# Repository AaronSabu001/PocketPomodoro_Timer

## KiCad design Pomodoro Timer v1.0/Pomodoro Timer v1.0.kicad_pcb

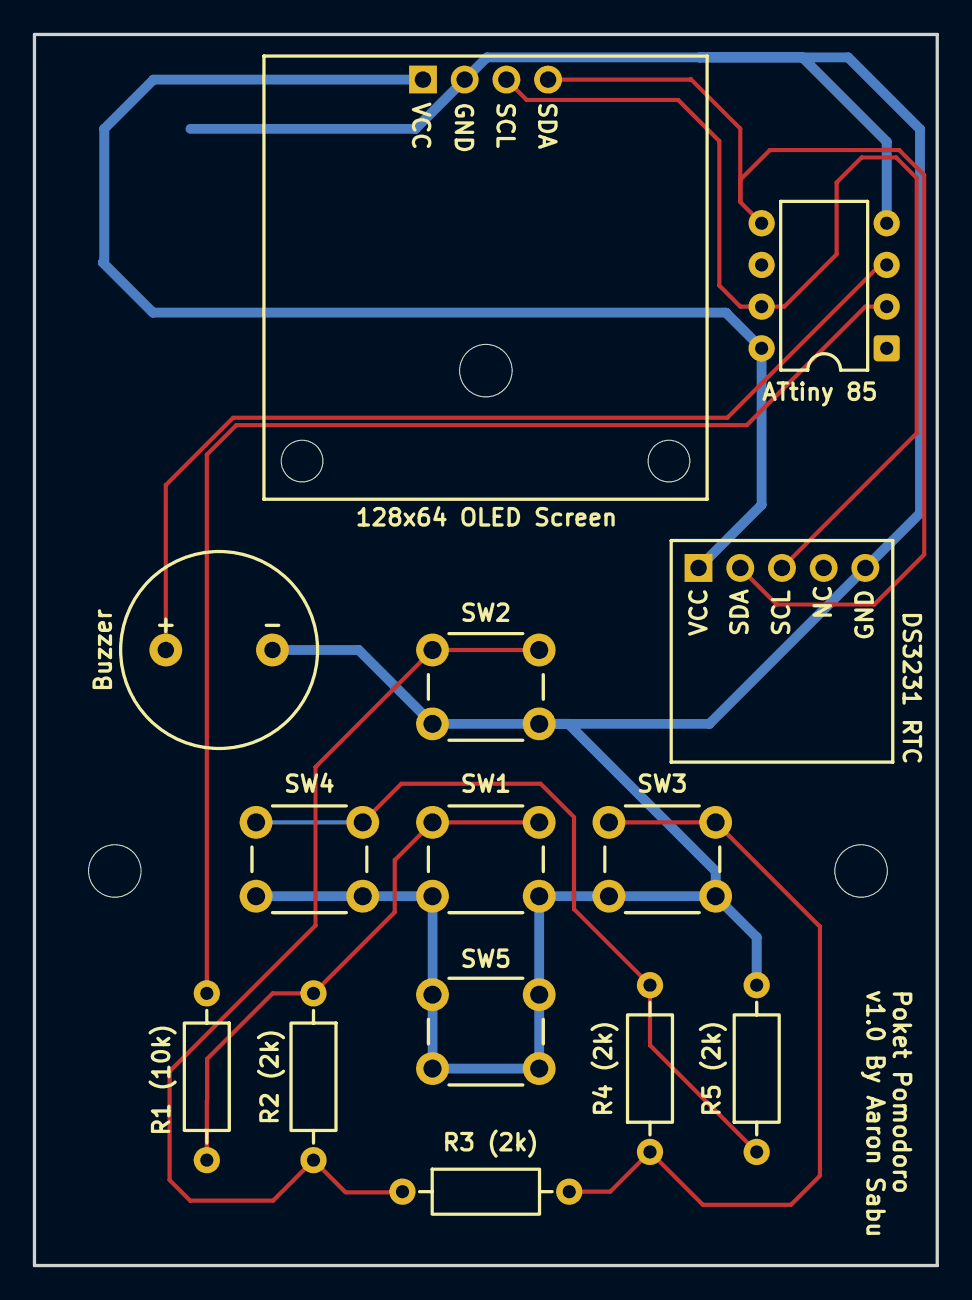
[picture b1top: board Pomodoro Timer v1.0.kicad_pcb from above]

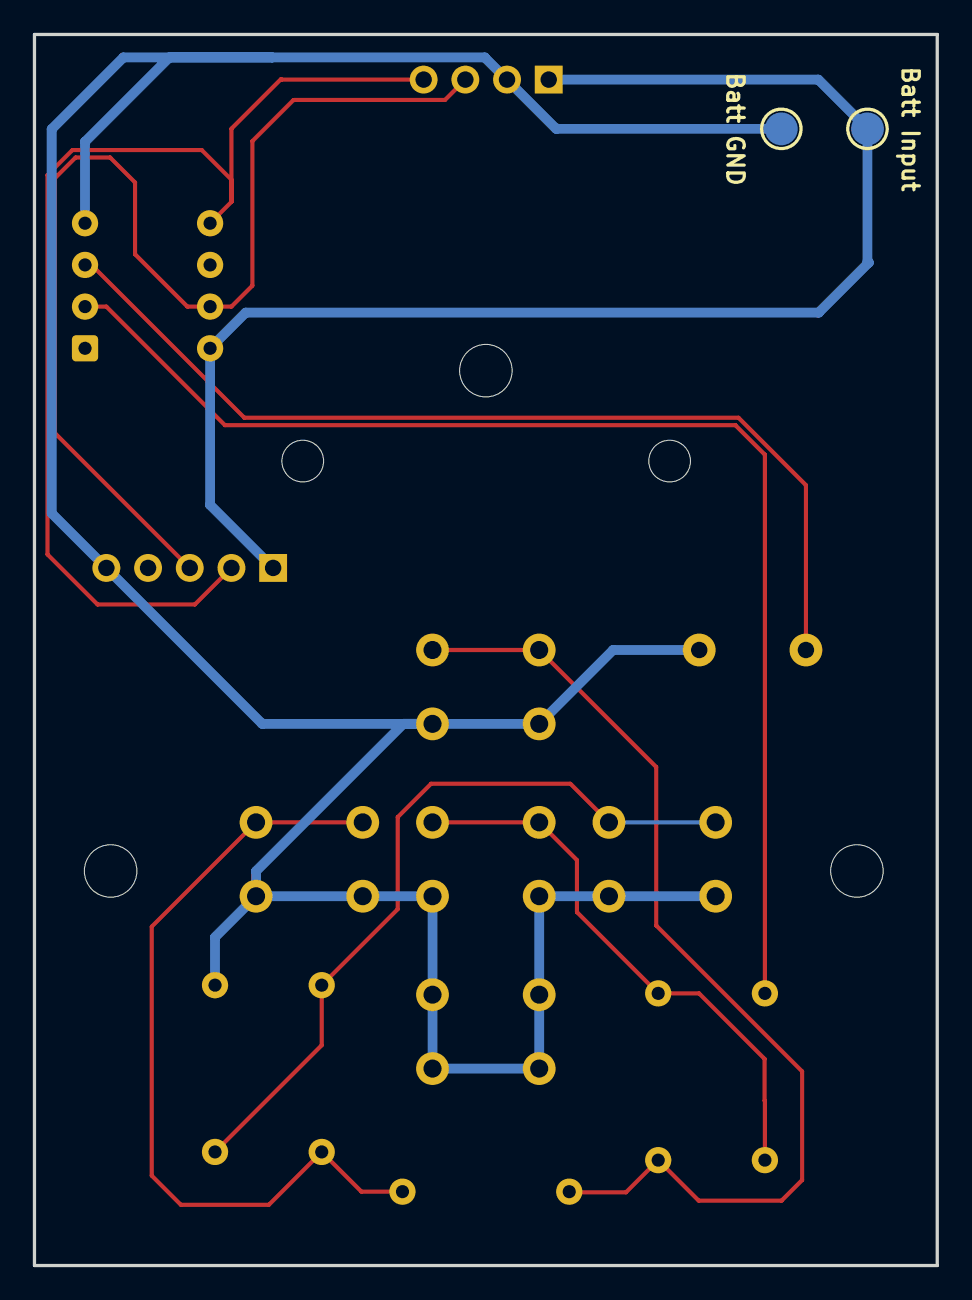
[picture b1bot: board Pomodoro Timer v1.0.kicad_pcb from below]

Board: 4 copper layers, 55.0 x 75.0 mm, 18 parts (2 on the bottom side), 10 nets.

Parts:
128x64 OLED Screen: 128x64 OLED; SSD1306_OLED_Module _I2C
ATtiny 85: ATtiny85-20P; DIP-8_W7.62mm
Batt GND: BT_Pad_Neg; TestPoint_Pad_D2.0mm
Batt Input: BT_Pad_Pos; TestPoint_Pad_D2.0mm
Buzzer: Buzzer; 6.5mm Pitch Buzzer
DS3231 RTC: DS3231 RTC; DS3231 I2C RTC Module
M3 Hole, M3 Hole#2: MountingHole_3.2mm_M3
R1 (10k): 10k; R_Axial_DIN0207_L6.3mm_D2.5mm_P10.16mm_Horizontal
R2 (2k), R3 (2k), R4 (2k), R5 (2k): 2k; R_Axial_DIN0207_L6.3mm_D2.5mm_P10.16mm_Horizontal
SW1, SW2, SW3, SW4, SW5: SW_Push; SW_PUSH_6mm

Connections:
/Button: ATtiny 85.2 (XTAL1/PB3), R1 (10k).1
/Buzzer: ATtiny 85.3 (XTAL2/PB4), Buzzer.1 (+)
/SCL: 128x64 OLED Screen.4 (SCL), ATtiny 85.7 (PB2), DS3231 RTC.4 (SCL)
/SDA: 128x64 OLED Screen.3 (SDA), ATtiny 85.5 (AREF/PB0), DS3231 RTC.3 (SDA)
/VCC: 128x64 OLED Screen.1 (VCC), ATtiny 85.8 (VCC), Batt Input.1, DS3231 RTC.1 (VCC)
GND: 128x64 OLED Screen.2 (GND), ATtiny 85.4 (GND), Batt GND.1, Buzzer.2 (-), DS3231 RTC.2 (GND), R5 (2k).2, SW1.2, SW2.2, SW3.2, SW4.2, SW5.1, SW5.2
unnamed: R1 (10k).2, R2 (2k).1, SW1.1
unnamed: R2 (2k).2, R3 (2k).1, SW2.1
unnamed: R3 (2k).2, R4 (2k).1, SW3.1
unnamed: R4 (2k).2, R5 (2k).1, SW4.1

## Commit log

2026-06-09 Initial commit: Base ATtiny85 schematic and OLED footprint
2026-06-09 Renamed folder for clarity
2026-06-09 Added misc files
2026-06-09 Added ATtiny code folder
